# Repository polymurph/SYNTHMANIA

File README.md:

# SYNTHMANIA

## TODOs

28.11.2021

-> Timmi:
  
 research functionality of VCO VCA VCF ADSR. 
 
 https://www.thomann.de/blog/en/modular-synthesizers-explained-simply/

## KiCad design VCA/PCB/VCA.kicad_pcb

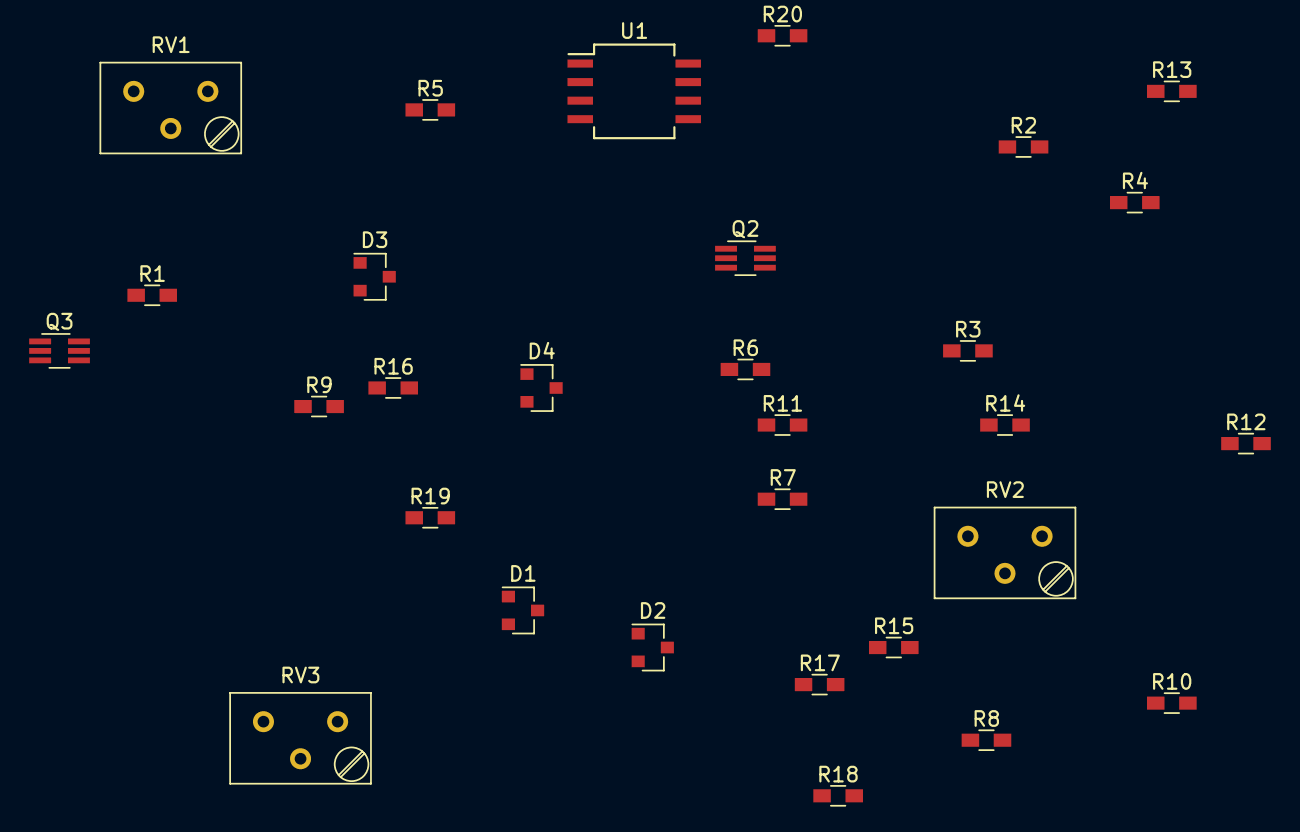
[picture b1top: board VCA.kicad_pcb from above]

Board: 2 copper layers, 30 parts (0 on the bottom side), 23 nets, no tracks yet.

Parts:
D1, D2, D3, D4: BAT54; D_SOT-23_ANK
Q2: BC846ASQ-T1; SOT-363_SC-70-6_Handsoldering
Q3: BC846ASQ-T2; SOT-363_SC-70-6_Handsoldering
R1, R2, R3, R18, R19: 10k; R_0603_HandSoldering
R4: 8k2; R_0603_HandSoldering
R5: 12k; R_0603_HandSoldering
R6, R7: 33k; R_0603_HandSoldering
R8: 15k; R_0603_HandSoldering
R9, R14: 100; R_0603_HandSoldering
R10, R12, R13: 1k5; R_0603_HandSoldering
R11: 3k3; R_0603_HandSoldering
R15, R16: 1k; R_0603_HandSoldering
R17: 470k; R_0603_HandSoldering
R20: 470; R_0603_HandSoldering
RV1, RV2: 1k; Potentiometer_Trimmer_Bourns_3299Y
RV3: 100k; Potentiometer_Trimmer_Bourns_3299Y
U1: NE5532; SO-8_5.3x6.2mm_Pitch1.27mm

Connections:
+12V: D1.1, D3.1, R4.1, RV2.2, RV3.1, U1.8
-12V: D2.2, D4.2, R5.2, R12.2, U1.4
/VCA 1/CV_IN: D1.2, D2.1, R2.1
/VCA 1/IN: D3.2, D4.1, R8.1
GNDA: R9.2, R14.2, R18.2, RV3.3, U1.2
unnamed: R1.2, R2.2, R3.1, U1.3
unnamed: R3.2, R6.1, U1.1
unnamed: R15.2, R19.1, U1.5
unnamed: R19.2, R20.1, U1.7
unnamed: R6.2, R7.2
unnamed: R11.2, R12.1
unnamed: Q2.1, Q3.4, R11.1
unnamed: Q2.2, R8.2, R9.1
unnamed: Q2.6, R10.2, R15.1
unnamed: Q3.3, R13.2, R16.1
unnamed: Q3.5, R14.1
unnamed: R4.2, RV1.1
unnamed: R5.1, RV1.3
unnamed: R7.1, RV1.2
unnamed: R10.1, RV2.1
unnamed: R13.1, RV2.3
unnamed: R16.2, R17.2, R18.1, U1.6
unnamed: R17.1, RV3.2

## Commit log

2021-11-28 work on VCA
2021-11-28 Added notes
2021-11-28 added empty adsr simulation project
2021-11-28 Added empty Simulations
2021-11-30 ADSR Simulation edit
2021-12-04 first crude outline of working vca simulation
2021-12-04 added linearizing diodes
2021-12-04 added bandlimit capacitors to opamps
2021-12-04 adapted C of feedback filters + added offset compensation
2021-12-04 optimized the cutoff frequencys for best pulse responce
2021-12-11 added new kicad project for VCA
2021-12-28 work on VCA cirquit
2021-12-28 started with the PCB cirquit design
2021-12-30 work on scematics
2021-12-30 cleaned up vca project
2021-12-30 determined needed offset circuit
2021-12-30 work on simpulation
2022-01-01 working stable simulation
2022-01-01 scematic design of vca
